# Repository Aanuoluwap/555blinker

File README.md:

# 555 Blinker & ESP32 Projects

This repository contains electronics design projects created using KiCad.

## Projects

### 1. 555 Blinker (Root)

A classic Astable Multivibrator circuit using the NE555 timer IC.

**Components:**
- **U1**: NE555D (SOIC-8)
- **R1**: 1kΩ Resistor (1206)
- **R2**: 68kΩ Resistor (1206)
- **R3**: 8.2kΩ Resistor (1206)
- **C2**: 10µF Tantalum Capacitor (EIA-3216-18)
- **D1**: LED (1206)
- **J1**: 1x02 Pin Header (2.54mm)

**Function:**
The circuit is configured as an astable multivibrator, flashing the LED (D1). The frequency is determined by R2, R3, and C2.

### 2. Project 2: ESP32 Build ✅ Complete

Located in `Priject_2__ESP32_build/`.

A compact 2-layer ESP32 temperature & humidity sensor board (55.3 × 34.5 mm). An ESP32-WROOM-32 module reads an AM2302 (DHT22) sensor, powered from a 2-pin input through an AMS1117-3.3 regulator. The module's PCB antenna overhangs the board edge, as Espressif recommends, so there is no copper beneath it.

**Components:**
- **U2**: ESP32-WROOM-32 module
- **U1**: AMS1117-3.3 LDO regulator (SOT-223)
- **U3**: AM2302 / DHT22 temperature & humidity sensor, data on **IO15**
- **R1**: 4.7kΩ pull-up on the sensor data line (1206)
- **R2, C3**: 10kΩ pull-up + 1µF cap on **EN** (reset RC)
- **R3**: 10kΩ pull-up on **IO0** (boot strap)
- **SW1 / SW2**: RESET and BOOT tactile buttons (TL3342)
- **C1 / C2**: 10µF input and 22µF output tantalum capacitors (EIA-3216-18)
- **J1**: 1x02 power input header (pin 1 = VIN, pin 2 = GND)

**Design status:**
- ERC: 0 errors, 0 warnings
- DRC: 0 errors, 0 unconnected items, PCB matches schematic. The only warnings are for the module's silkscreen, which is intentionally clipped where the antenna overhangs the edge.
- Solid GND pour on both layers with stitching vias; 0.5–0.6 mm power tracks, 0.25 mm signal tracks, 0.2 mm clearance (fits JLCPCB standard 2-layer rules)

**Manufacturing files** (`Priject_2__ESP32_build/fab/`):
- `Priject_2__ESP32_build-gerbers.zip`: Gerbers + Excellon drill files, ready to upload to a PCB fab
- `Priject_2__ESP32_build-BOM.csv`: bill of materials
- `Priject_2__ESP32_build-top-pos.csv`: pick-and-place positions for assembly

To flash the ESP32: hold **BOOT** (SW2), tap **RESET** (SW1), then release BOOT.

## Directory Structure

```
.
├── 555 blinker.kicad_pro    # 555 Blinker Project File
├── 555 blinker.kicad_sch    # Schematic
├── 555 blinker.kicad_pcb    # PCB Layout
└── Priject_2__ESP32_build/  # ESP32 Project Folder
    ├── Priject_2__ESP32_build.kicad_sch
    ├── Priject_2__ESP32_build.kicad_pcb
    └── fab/                 # Gerber zip, BOM, placement file
```

## Tools Used

- **KiCad EDA**: [https://www.kicad.org/](https://www.kicad.org/) (Version 8.0 or later recommended)

## License

This project is licensed under the MIT License - see the [LICENSE](LICENSE) file for details.

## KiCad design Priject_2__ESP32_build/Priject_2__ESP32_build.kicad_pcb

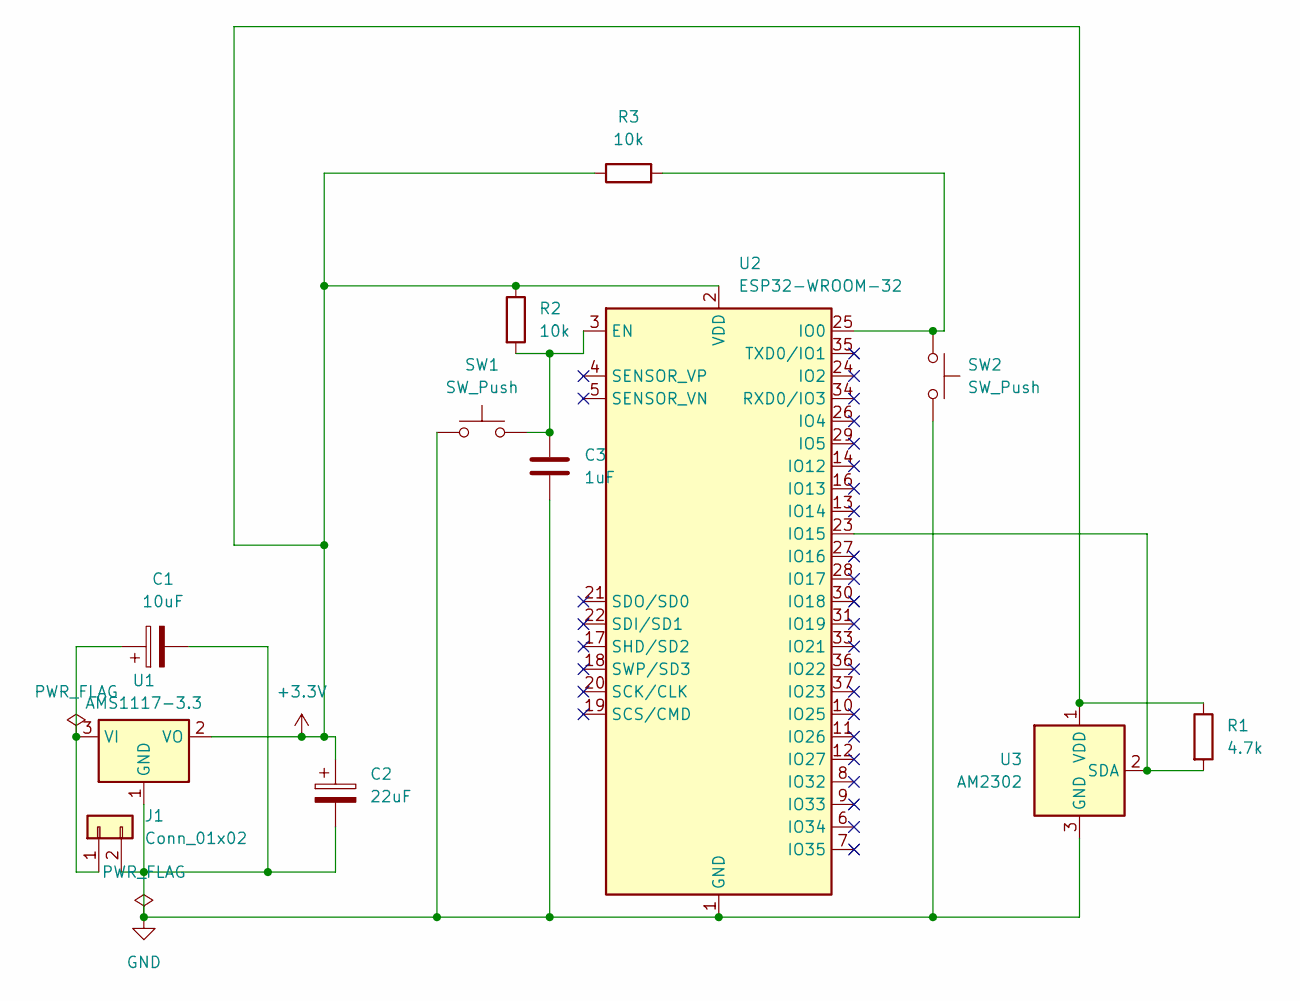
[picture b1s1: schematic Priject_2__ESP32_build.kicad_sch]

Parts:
C1: 10uF; CP_EIA-3216-18_Kemet-A
C2: 22uF; CP_EIA-3216-18_Kemet-A
C3: 1uF; C_0805_2012Metric
J1: Conn_01x02; PinHeader_1x02_P2.54mm_Vertical_SMD_Pin1Right
R1: 4.7k; R_1206_3216Metric
R2, R3: 10k; R_1206_3216Metric
SW1, SW2: SW_Push; SW_SPST_TL3342
U1: AMS1117-3.3; SOT-223-3_TabPin2
U2: ESP32-WROOM-32
U3: AM2302; ASAIR_AM2302_P2.54mm_Vertical

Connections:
+3.3V: C2.1, R1.1, R2.1, R3.1, U1.2 (VO), U2.2 (VDD), U3.1 (VDD)
GND: C1.2, C2.2, C3.2, J1.2, SW1.1, SW2.2, U1.1 (GND), U2.1 (GND), U2.15 (GND), U2.38 (GND), U2.39 (GND), U3.3 (GND), U3.4 (GND)
unnamed: C1.1, J1.1, U1.3 (VI)
unnamed: C3.1, R2.2, SW1.2, U2.3 (EN)
unnamed: R3.2, SW2.1, U2.25 (IO0)
unnamed: R1.2, U2.23 (IO15), U3.2 (SDA)

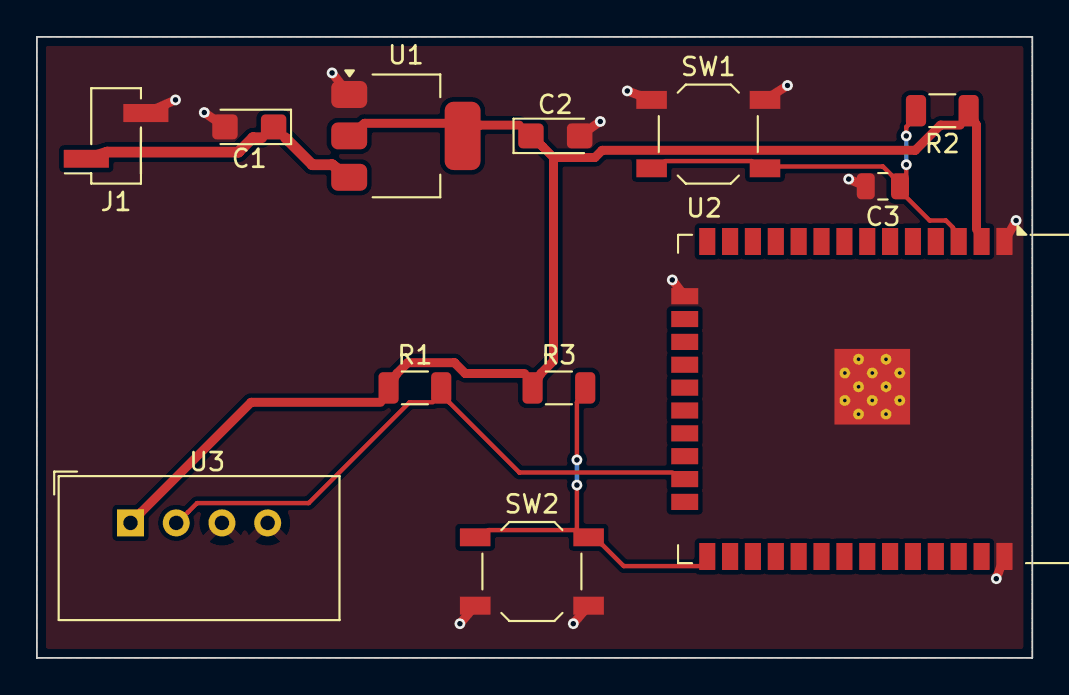
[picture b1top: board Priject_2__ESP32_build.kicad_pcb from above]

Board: 2 copper layers, 55.3 x 34.5 mm, 12 parts (0 on the bottom side), 6 nets.

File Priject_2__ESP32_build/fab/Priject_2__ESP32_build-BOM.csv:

Comment,Designator,Footprint,Quantity,LCSC Part #
10uF,C1,CP_EIA-3216-18_Kemet-A,1,
22uF,C2,CP_EIA-3216-18_Kemet-A,1,
1uF,C3,C_0805_2012Metric,1,
Conn_01x02,J1,PinHeader_1x02_P2.54mm_Vertical_SMD_Pin1Right,1,
4.7k,R1,R_1206_3216Metric,1,
10k,"R2,R3",R_1206_3216Metric,2,
SW_Push,"SW1,SW2",SW_SPST_TL3342,2,
AMS1117-3.3,U1,SOT-223-3_TabPin2,1,
ESP32-WROOM-32,U2,ESP32-WROOM-32,1,
AM2302,U3,ASAIR_AM2302_P2.54mm_Vertical,1,

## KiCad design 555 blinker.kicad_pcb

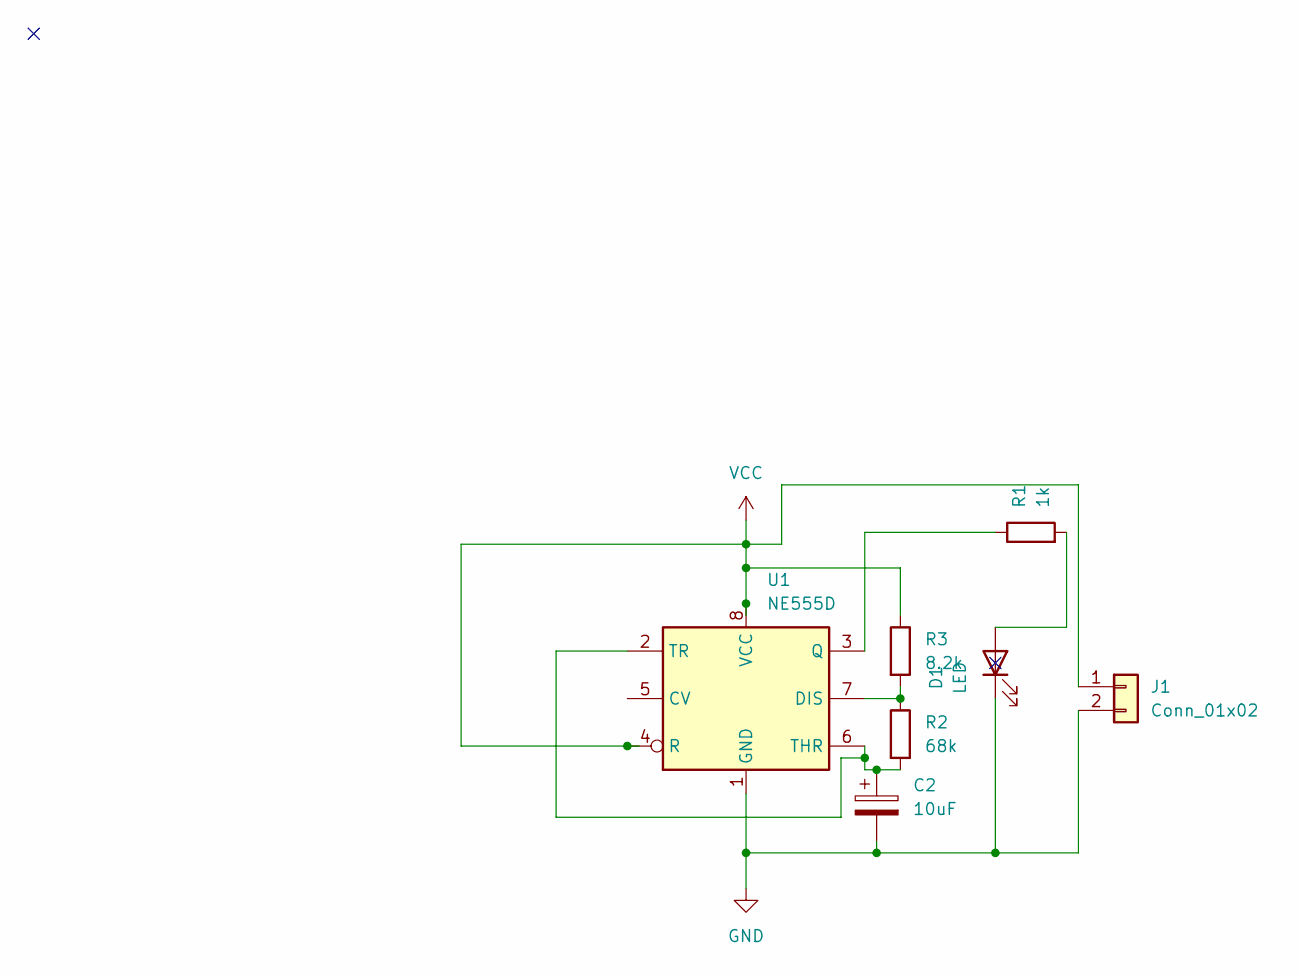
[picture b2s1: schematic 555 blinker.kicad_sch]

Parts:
C2: 10uF; CP_EIA-3216-18_Kemet-A
D1: LED; LED_1206_3216Metric
J1: Conn_01x02; PinHeader_1x02_P2.54mm_Vertical
R1: 1k; R_1206_3216Metric
R2: 68k; R_1206_3216Metric
R3: 8.2k; R_1206_3216Metric
U1: NE555D; SOIC-8_3.9x4.9mm_P1.27mm

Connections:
GND: C2.2, D1.1 (K), J1.2, U1.1 (GND)
unnamed: D1.2 (A), R1.2
unnamed: R2.1, R3.2, U1.7 (DIS)
unnamed: R1.1, U1.3 (Q)
unnamed: C2.1, R2.2, U1.2 (TR), U1.6 (THR)
VCC: J1.1, R3.1, U1.4 (R), U1.8 (VCC)

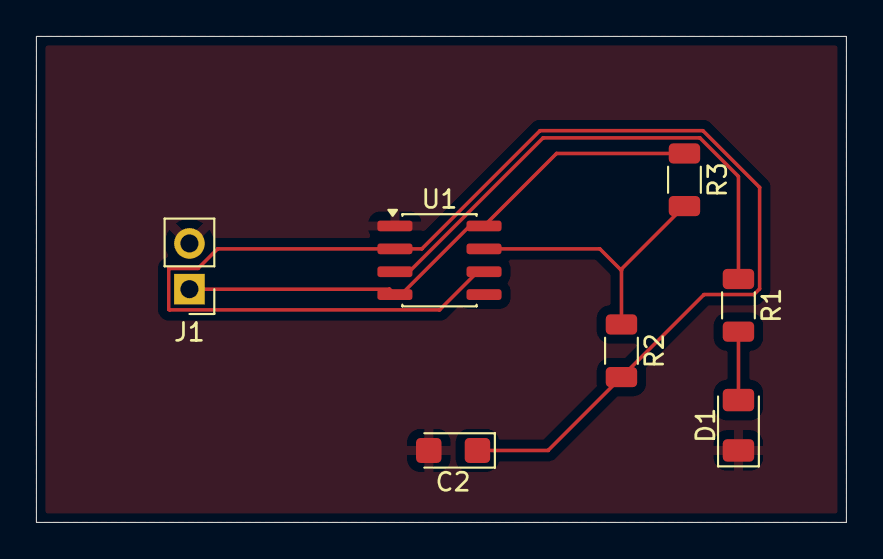
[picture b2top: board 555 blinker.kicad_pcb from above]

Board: 2 copper layers, 45.0 x 27.0 mm, 7 parts (0 on the bottom side), 6 nets.

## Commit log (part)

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2025-12-10 Initial committ
2025-12-10 Clean up repository and add README.md
    Ignored and removed KiCad backup directories, report files, and other generated artifacts.
    Added a README.md file describing the 555 Blinker and ESP32 projects.
2025-12-10 Clean up repository, add README and MIT License
    - Removed KiCad backup directories and generated report files.
    - Updated .gitignore to exclude backups and reports.
    - Added README.md describing the projects.
    - Added MIT License with owner Aanuoluwapo Oniyide.
2025-12-10 Add 3D view image of the PCB to README
    - Created 'images' directory.
    - Added '555_blinker_3d_view.png'.
    - Updated README.md to display the image.
